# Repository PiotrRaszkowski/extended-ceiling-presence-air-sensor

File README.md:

# Extended ceiling presence + air sensor

A small ceiling-mounted sensor for Home Assistant, about the size of a smoke detector (Ø80 × 30 mm, or Ø100 if you want more room inside). One per room. It tells you whether someone is in the room, even if they're sitting still, and how the air is doing.

It combines:

- 24 GHz mmWave radar (HLK-LD2410B) for presence, including people who aren't moving
- PIR (HC-SR602) for fast motion detection when someone walks in
- ENS160 + AHT21 for air quality (eCO2, TVOC, AQI), temperature and humidity, in a separate ventilated chamber so the electronics don't heat the sensors
- BH1750 light sensor, so lights only come on when it's actually dark
- ESP32-S3-Zero running [ESPHome](https://esphome.io), powered from 12 V

Parts cost about 100 zł (~€24) from AliExpress or about 160 zł (~€38) from a single seller on Allegro in Poland. The enclosure prints in PETG without supports and every board is held by press-fit crush ribs, so there are no screws inside and glue shouldn't be needed.

## Project status

| Part | Status |
|---|---|
| Firmware | Validates and compiles with ESPHome 2026.10.0. Not yet confirmed on a finished unit. |
| Electronics | Wiring designed around these modules. Do the bench test from [assembly](docs/assembly.md) before closing the box. |
| Enclosure Ø100 (v18, [`hardware/d100/`](hardware/d100/)) | The Ø100 prototype was printed in PETG and installed in a kitchen. In it the radar saw noise on every gate ([why](docs/printing.md#the-radar-window)), so v15/v16 thin the window to 0.8 mm and put the radar on posts 6.2 mm above it. v16 also widens the ENS160 pass-through and tightens the crush ribs a little; v17/v18 add snap lips that hold the radar down (the seat was checked with a test print). |
| Enclosure Ø80 (v18, current) | v12 was printed in PETG and every module went into its seat (photos below). v13 tightens the BH1750 seat by 0.05 mm; v14 adds a seat for the [Dupont hub](docs/wiring.md#dupont-hub) and moves the ENS160 pass-through; v16 puts the radar on posts above a 0.8 mm window, as in Ø100. Print `11_seat_test_fit.stl` first anyway, since fit depends on your printer. |

Issues and photos of your build are welcome.

**Next version:** [v2](v2/) replaces the jumpers and the hub with a round carrier PCB that every module plugs into, switches to the HLK-LD2412 radar (2.54 mm pins) and adds an optional SCD40/SCD41 for real CO2. It is designed but not built yet.

## Documentation

1. [Bill of materials](docs/bom.md): modules with Allegro and AliExpress links, passives, screws
2. [Wiring](docs/wiring.md): diagram, pin map, power notes
3. [Printing](docs/printing.md): filament, slicer settings, print order, fit calibration
4. [Firmware and Home Assistant](docs/firmware.md): flashing ESPHome, adding the device, entity list
5. [Assembly](docs/assembly.md): modules into seats, ceiling mount
6. [Tuning and automations](docs/tuning.md): radar range, temperature offset, example automations
7. [Enclosure source](docs/enclosure-source.md): OpenSCAD Customizer for other module sizes, CadQuery model, parameters, measured sizes

## Quick start

1. Buy the parts from the [BOM](docs/bom.md). Stick to the exact module types, because the seats are sized to them.
2. Print `10_press_fit_calibration.stl` and `11_seat_test_fit.stl` from [`hardware/stl/`](hardware/stl/), check the fit, then print `00_print_plate_all_parts.stl`.
3. Flash [`firmware/ceiling-sensor.yaml`](firmware/ceiling-sensor.yaml) over USB and wire everything on the bench.
4. Check in Home Assistant that every sensor reports, then assemble and mount it.
5. Tune the radar range and the temperature offset.

A printed Ø80 housing (v12) with every module pressed into its seat, seen from the ceiling side:

| | |
|---|---|
|  |  |

## Repository layout

```
firmware/        ESPHome config + secrets template
hardware/stl/    printable parts, Ø80
hardware/step/   the same parts as STEP
hardware/source/ CadQuery model, the same model for OpenSCAD (Customizer), wiring diagram generator
hardware/d100/   printable parts, Ø100 (STL + STEP)
v2/              next version: carrier PCB, LD2412, optional SCD4x (designed, not built yet)
homeassistant/   example automations
docs/            documentation and images
```

## Limitations

- eCO2 from the ENS160 is **estimated from VOCs**, not measured. It's fine for "the room is stuffy, open a window", not for exact ppm. If you need real CO2, add an SCD40 or MH-Z19C.
- There is no particulate (PM2.5) sensor.
- The radar sees through thin walls. Limit its range in Home Assistant, see [tuning](docs/tuning.md).

## License

[MIT](LICENSE): firmware, CAD source, models and docs.

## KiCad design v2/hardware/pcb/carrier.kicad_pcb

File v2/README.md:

# v2: carrier PCB (Ø100)

> **Status: designed, not built.** Nothing in this folder has been ordered, printed or tested yet. Several module dimensions come from product photos, not from a caliper. Go through [verify.md](docs/verify.md) before you order boards.

v1 works, but wiring it is fiddly: about twenty jumpers, a hand-made Dupont hub, and a radar with 1.27 mm pads. v2 puts all of that on a round two-layer PCB. Every module plugs into a female socket on the underside of the board, the board goes into the housing as one piece, and three M2 screws hold it.

## What changes compared with v1

| | v1 | v2 |
|---|---|---|
| Wiring | Jumpers + a perfboard hub | Carrier PCB, modules plug in |
| Radar | HLK-LD2410B, 1.27 mm pads | HLK-LD2412, 2.54 mm pins, longer range, better at still people |
| Power | S09 module, EN bridged by hand, capacitor on its pads | 3-pin switching regulator (K7805-1000R3 or any pin-compatible 7805 replacement) on the board |
| 12 V input | Wago | Keyed JST-XH connector, plus a diode against reverse polarity |
| USB + 12 V together | Not allowed | Allowed (a diode separates the ESP from the 5 V rail) |
| Room temperature / humidity | AHT21 on the ENS160 board (reads ~10 °C high: the ENS160 heater is next to it) | Separate SHT40 in its own walled, vented pocket |
| CO2 | eCO2 estimated from VOCs | Optional SCD40/SCD41 socket for real CO2 |
| Housing | Ø80 or Ø100 | Ø100 only; same ceiling base and bayonet as v1 |
| ESP | On the face | Under the PCB, in a socket: unplug it to flash over USB |

The PIR, BH1750, ENS160+AHT21 and ESP32-S3-Zero are the same boards as in v1.

| Modules under the PCB (PCB hidden) | Assembled |
|---|---|
|  |  |

## Order of work

1. Buy the parts: [bom.md](docs/bom.md).
2. Check the parts against the design: [verify.md](docs/verify.md). Print `20_pcb_fit_template.stl` and the housing first, then plug the modules in through the template.
3. Order the PCB (five boards cost about 10 USD including the cheapest shipping to Poland): [pcb.md](docs/pcb.md).
4. Solder sockets and power parts, flash the ESP, plug in the modules: [assembly.md](docs/assembly.md).
5. Firmware: [firmware.md](docs/firmware.md).

## Files

```
v2/firmware/          ESPHome config for v2 (+ optional scd4x.yaml)
v2/hardware/pcb/      KiCad board (carrier.kicad_pcb, KiCad 7 or newer)
v2/hardware/gerber/   Gerbers + drill files, zipped for JLCPCB
v2/hardware/stl/      housing, ceiling base, PCB fit template
v2/hardware/step/     the same as STEP
v2/hardware/source/   layout.py (positions, pins, nets) and the scripts that build the board,
                      the housing and the drawings from it
v2/docs/              documentation and images
```

`layout.py` is the only place where module positions, pin orders and nets are written down. The PCB, the housing, the schematic and the assembly drawing are all generated from it, so if a module turns out different, you fix one file and rebuild everything (see [verify.md](docs/verify.md)).

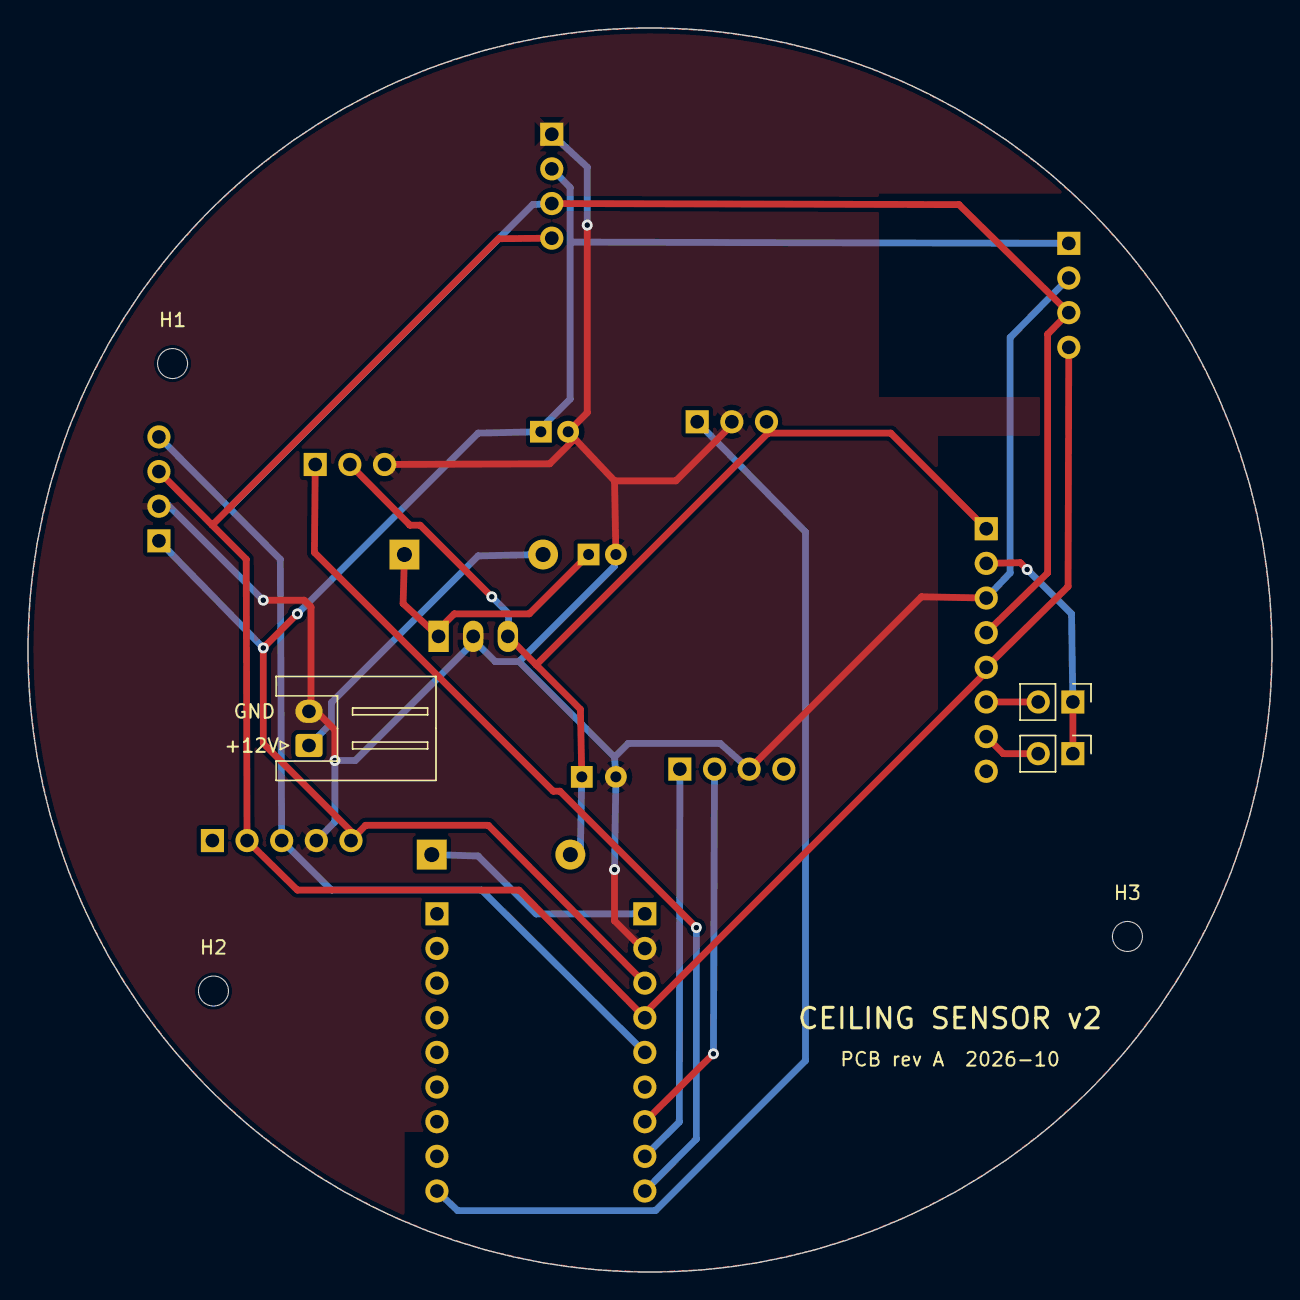
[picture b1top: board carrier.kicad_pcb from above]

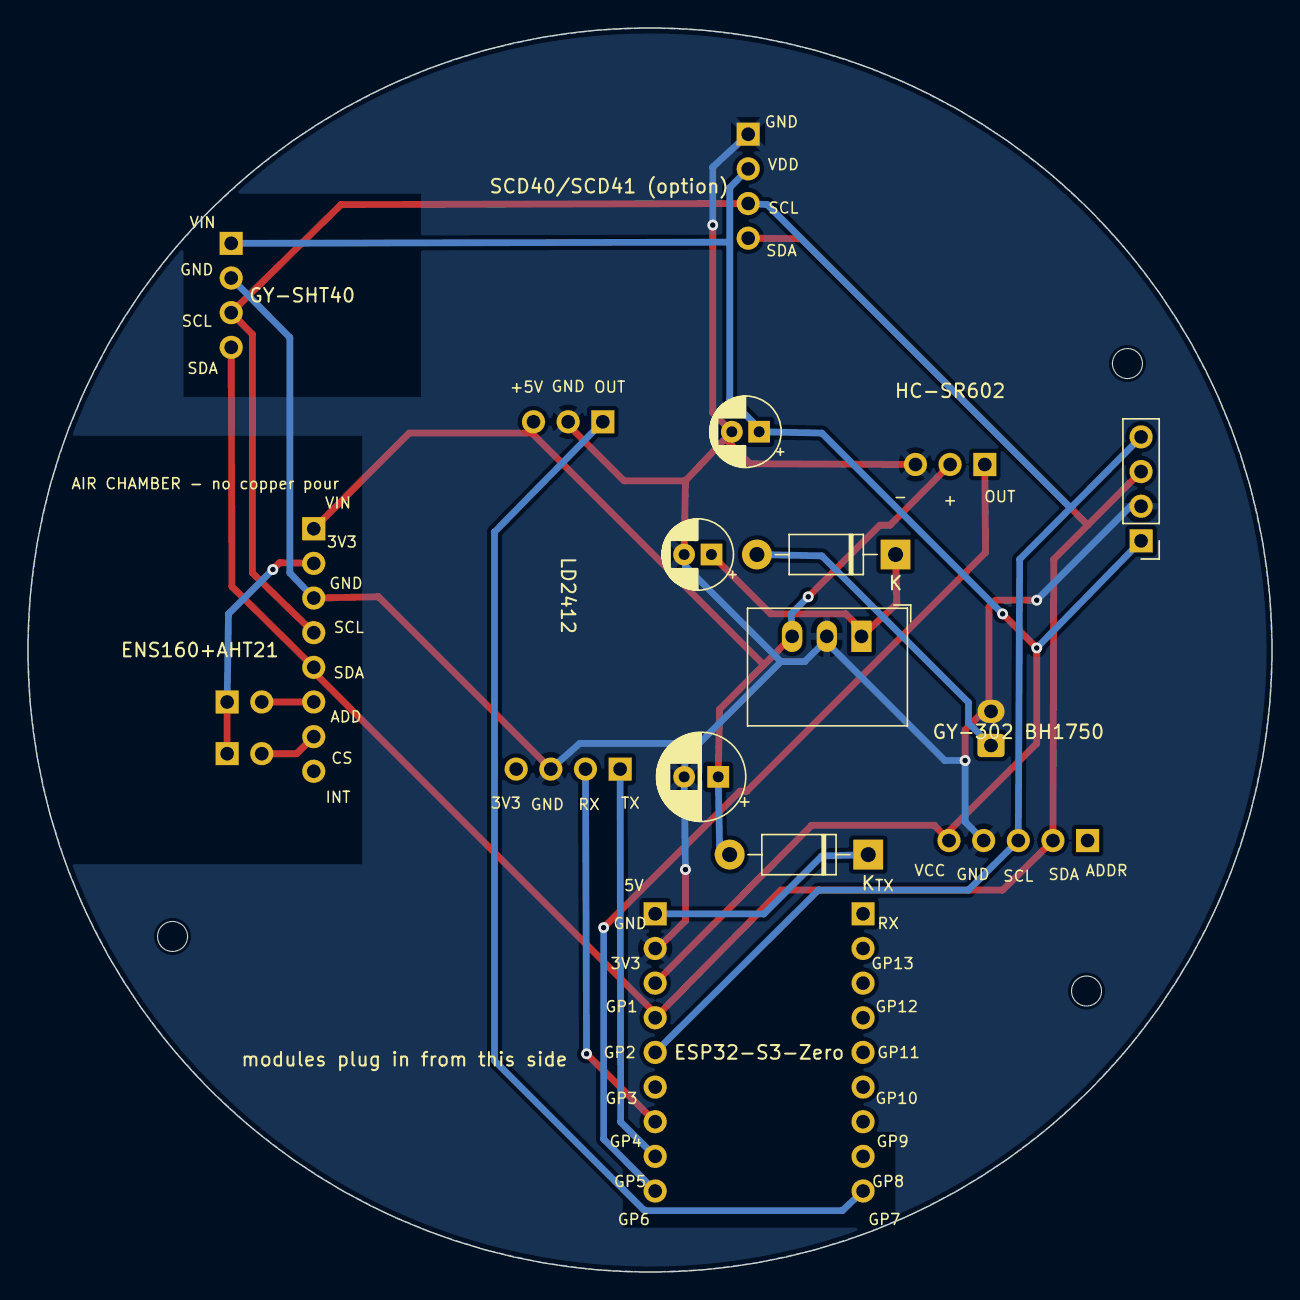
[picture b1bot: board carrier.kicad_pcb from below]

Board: 2 copper layers, 91.2 x 91.2 mm, 22 parts (16 on the bottom side), 15 nets.

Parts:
C1: 10uF 25V; CP_Radial_D5.0mm_P2.00mm
C2: 220uF 10V; CP_Radial_D6.3mm_P2.50mm
C3: 47uF 10V (with SCD4x); CP_Radial_D5.0mm_P2.00mm
CH1: ENS160 chamber walls (housing); ChamberWalls
CH2: SHT40 pocket walls (housing); PocketWalls
D1, D2: 1N5819; D_DO-41_SOD81_P10.16mm_Horizontal
H1, H2, H3: M2 to housing boss; MountingHole_2.2mm_M2
J1: 12V IN (JST-XH); JST_XH_S2B-XH-A_1x02_P2.50mm_Horizontal
J2: I2C expansion (not fitted); PinHeader_1x04_P2.54mm_Vertical
JP1: ADD strap; PinHeader_1x02_P2.54mm_Vertical
JP2: CS strap; PinHeader_1x02_P2.54mm_Vertical
U1: K7805-1000R3 / R-78E5.0-1.0; Converter_DCDC_RECOM_R-78E-0.5_THT
U2: ESP32-S3-Zero; Module_ESP
U3: LD2412; Module_RADAR
U4: HC-SR602; Module_PIR
U5: GY-302 BH1750; Module_BH
U6: ENS160+AHT21; Module_ENS
U7: SCD40/SCD41 (option); Module_SCD
U8: GY-SHT40; Module_SHT

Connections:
+3V3: C3.1, J2.1, U2.12 (3V3), U5.5 (VCC), U7.2 (VDD), U8.1 (VIN)
+5V: C2.1, D2.2, U1.3, U3.7 (+5V), U4.2 (+), U6.1 (VIN)
ENS_3V3: JP1.1, JP2.1, U6.2 (3V3)
ENS_ADD: JP1.2, U6.6 (ADD)
ENS_CS: JP2.2, U6.7 (CS)
ESP_5V: D2.1, U2.10 (5V)
GND: C1.2, C2.2, C3.2, J1.2, J2.2, U1.2, U2.11 (GND), U3.3 (GND), U3.6 (GND), U4.3 (-), U5.4 (GND), U6.3 (GND), U7.1 (GND), U8.2 (GND)
PIR_OUT: U2.18 (GP6), U4.1 (OUT)
RADAR_OUT: U2.9 (GP7), U3.5 (OUT)
RADAR_RX: U2.16 (GP4), U3.2 (RX)
RADAR_TX: U2.17 (GP5), U3.1 (TX)
SCL: J2.4, U2.14 (GP2), U5.3 (SCL), U6.4 (SCL), U7.3 (SCL), U8.3 (SCL)
SDA: J2.3, U2.13 (GP1), U5.2 (SDA), U6.5 (SDA), U7.4 (SDA), U8.4 (SDA)
VIN: C1.1, D1.1, U1.1
VIN_RAW: D1.2, J1.1

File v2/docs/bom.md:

# v2 bill of materials

Prices in PLN, checked in October 2026. Modules that are the same as in v1 link to the v1 [BOM](../../docs/bom.md).

## Modules

| Ref | Part | Where | Notes |
|---|---|---|---|
| U2 | Waveshare ESP32-S3-Zero | as v1 | Get the **ESP32-S3-Zero-M** variant (headers already soldered), or solder the headers yourself on the side **without** components. |
| U3 | Hi-Link HLK-LD2412 radar, 11 × 28 mm | [Allegro, ~25 zł](https://allegro.pl/oferta/16441330303); AliExpress: Hi-Link's own store, search "HLK-LD2412" | Take the version **with pins**. The pins must come out of the back (the side without the antenna patches and the chip). Check before soldering anything, see [verify.md](verify.md). |
| U4 | HC-SR602 PIR | as v1 | Header pins out of the back (away from the lens), as in v1. |
| U5 | GY-302 BH1750 | as v1 | Header pins out of the side without the sensor chip, as in v1. |
| U6 | ENS160 + AHT21 combo | as v1 | Header on the **component** side this time: the board sits components up. If your v1 board has the header on the other side, desolder it and fit a new one. |
| U8 | GY-SHT40 temperature/humidity module (purple, VIN/GND/SCL/SDA, ~13 × 10 mm) | [AliExpress, ~17 zł](https://pl.aliexpress.com/item/1005013050830731.html) | Room temperature and humidity. Header on the side **without** the sensor (the sensor faces the room). SHT41 boards with the same layout work too. |
| U7 | SCD40 or SCD41 module (optional) | [AliExpress, ~62 zł](https://pl.aliexpress.com/item/1005011652313734.html), the GND/VDD/SCL/SDA board | Solder the header on the **sensor** side. SCD41 has the wider calibrated range (up to 5000 ppm); for a kitchen or living room SCD40 is enough. |

## Parts on the PCB

| Ref | Part | Qty | Notes |
|---|---|---|---|
| U1 | Switching regulator 5 V 1 A, 3-pin 7805 replacement (Mornsun K7805-1000R3, RECOM R-78E5.0-1.0, or a generic one such as [this Allegro offer, ~3 zł](https://allegro.pl/oferta/18597276546)) | 1 | Pinout must be 1 = VIN, 2 = GND, 3 = 5 V (same as an LM7805). Max 15 mm tall when standing. Not a linear 7805: that would burn ~1.4 W inside the box. |
| D1, D2 | 1N5819 Schottky diode (DO-41) | 2 | D1: reverse polarity protection. D2: lets you plug USB-C into the ESP while 12 V is connected. |
| C1 | Electrolytic 10 µF 25 V, Ø5 mm, 2 mm pitch | 1 | Regulator input. 35 V or 50 V is fine too. |
| C2 | Electrolytic 220 µF 10 V (or 16 V), Ø6.3 mm, 2.5 mm pitch | 1 | 5 V rail; the same capacitor as in v1. |
| C3 | Electrolytic 47 µF 10 V, Ø5 mm, 2 mm pitch | 1 | Only with the SCD4x (it draws up to ~200 mA peaks from 3.3 V). |
| J1 | JST-XH 2-pin header, **right angle** (S2B-XH-A) + a 2-pin XH plug with wires | 1 | Pre-crimped "JST XH 2pin" leads are cheap on Allegro and AliExpress. A straight (vertical) header will not fit under the ceiling base. |
| | Female pin header 2.54 mm, 1 × 40, 8.5 mm tall | 2 strips | Cut into 2 × 9, 1 × 8, 1 × 5, 2 × 4, 2 × 3 (45 pins; you lose one pin per cut). |
| | M2 × 6 self-tapping screw for plastics (PT / "wkręt do tworzyw") | 3 | Holds the PCB on the bosses. |
| | PCB | 1 | [pcb.md](pcb.md): 5 boards from JLCPCB, ~4 USD + shipping. |

Everything else (ceiling base screws, 12 V supply, PETG) is the same as v1.

## What you no longer need from v1

S09 converter, perfboard hub, Dupont jumpers, Wago connector, the LD2410B and its cable.
